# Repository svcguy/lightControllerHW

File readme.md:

Schematic and PCB for my workbench light controller

The workbench light is a 1m strip of APA102C Cool White LEDs, 144 LEDS/m.

The controller is a custom PCB that uses capacitive touch buttons and is based on a PIC16F1719

The light housing is made from an aluminum commercial door threshold and some 3/8" black gas piping.

This is a work-in-progress with more information to come

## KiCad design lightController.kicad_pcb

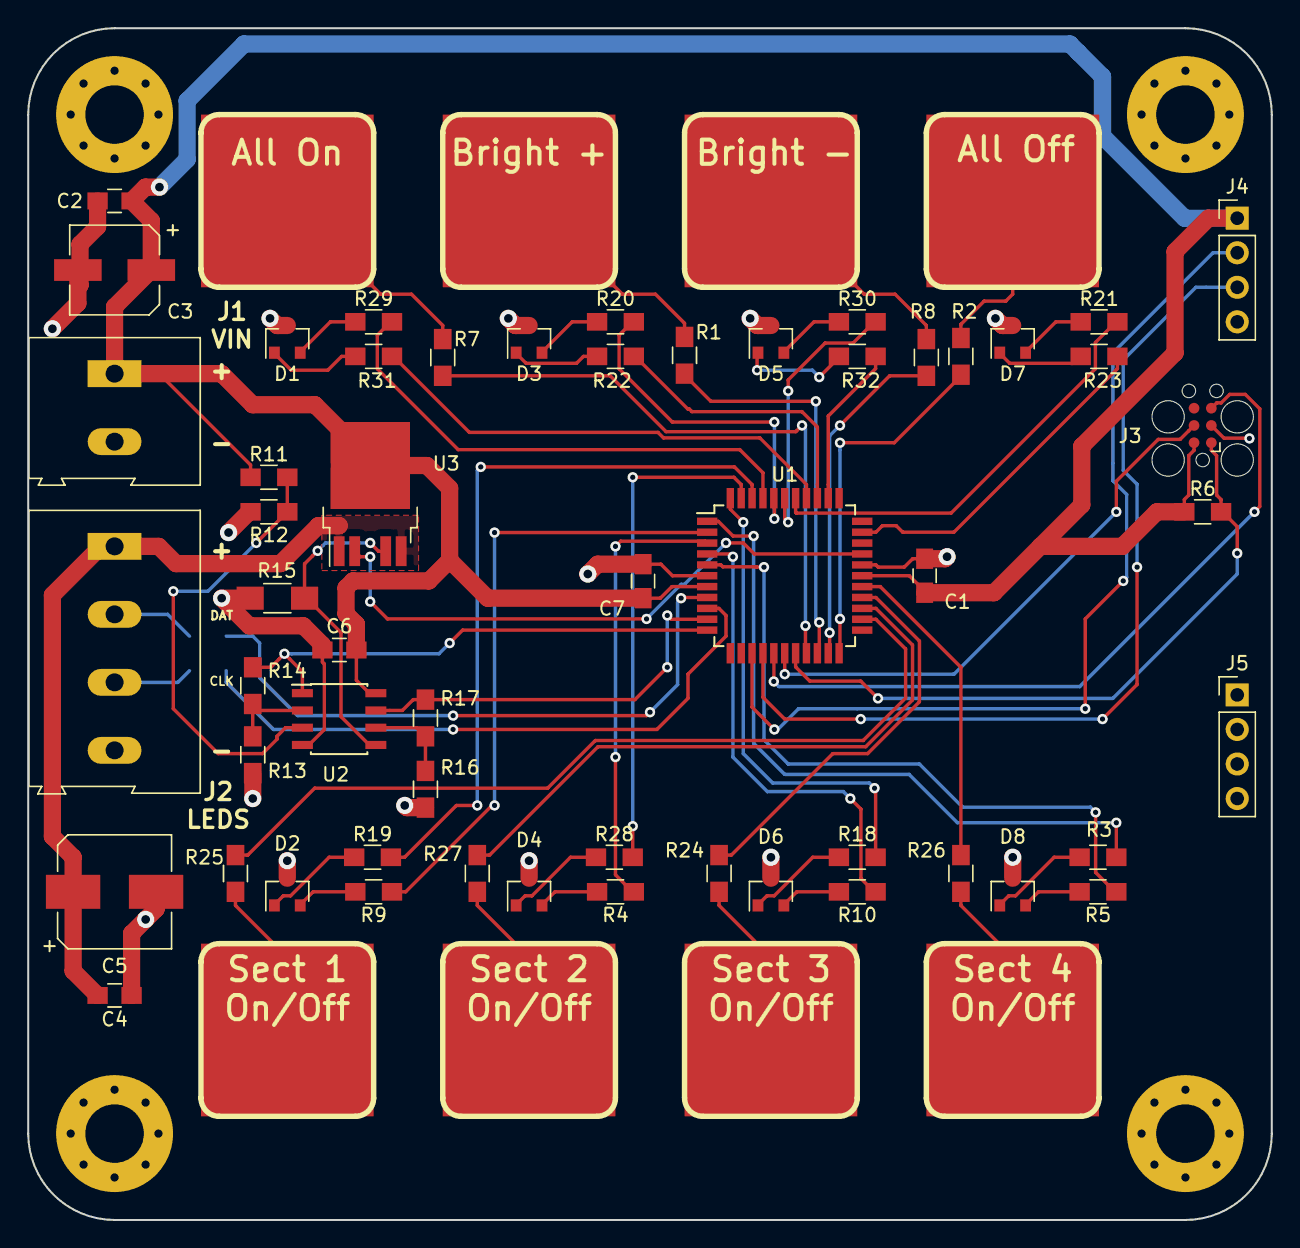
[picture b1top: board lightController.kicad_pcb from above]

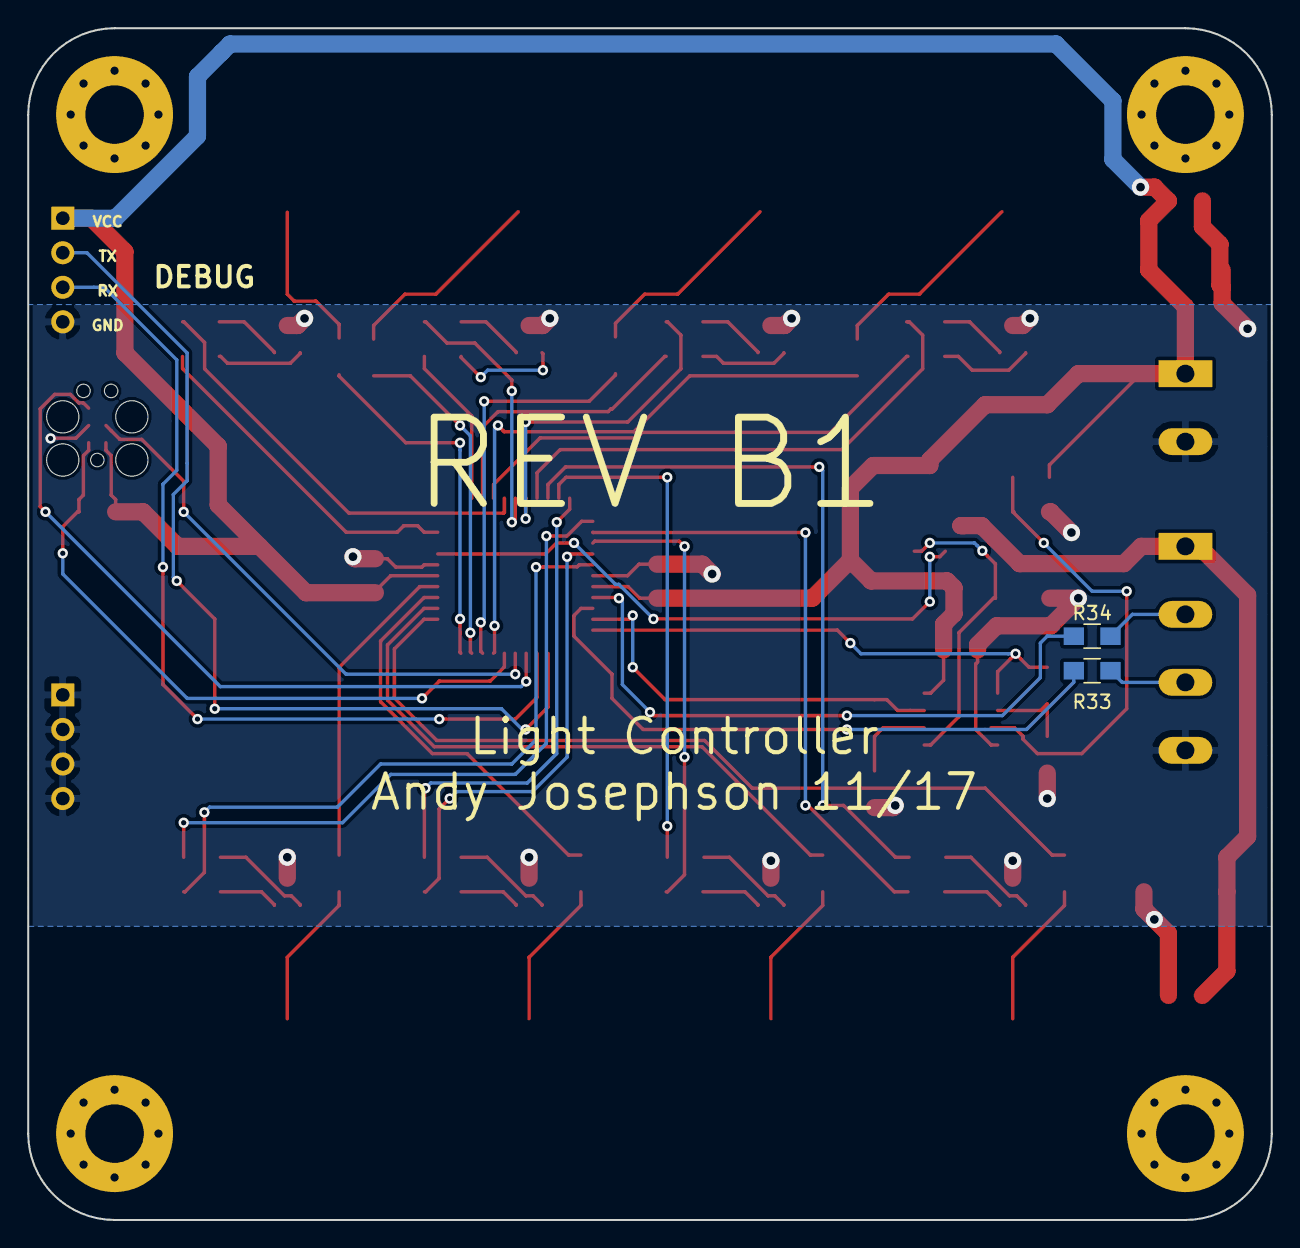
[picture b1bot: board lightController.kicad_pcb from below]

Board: 2 copper layers, 91.4 x 87.6 mm, 69 parts (2 on the bottom side), 67 nets.

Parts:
C1, C2, C4, C6, C7: 0.1uF; C_0805_HandSoldering
C3: 100uF; CP_Elec_6.3x5.3
C5: 1000uF; CP_Elec_8x10.5
D1: LED_LIGHT_ON; SOT-23
D2: LED_SECT_0; SOT-23
D3: LED_BRIGHT+; SOT-23
D4: LED_SECT_1; SOT-23
D5: LED_BRIGHT-; SOT-23
D6: LED_SECT_2; SOT-23
D7: LED_LIGHT_OFF; SOT-23
D8: LED_SECT_3; SOT-23
H1, H2, H3, H4: HOLE; MountingHole_4.3mm_M4_Pad_Via
J1: VIN; TerminalBlock_Altech_AK300-2_P5.00mm
J2: LED STRIP; TerminalBlock_Altech_AK300-4_P5.00mm
J3: ICSP; Tag-Connect_TC2030-IDC-FP
J4: DEBUG; Pin_Header_Straight_1x04_Pitch2.54mm
J5: GND; Pin_Header_Straight_1x04_Pitch2.54mm
R1, R2, R7, R8, R16, R24, R25, R26, R27, R33, R34: 1k; R_0805_HandSoldering
R3, R4, R5, R9, R10, R18, R19, R20, R21, R22, R23, R28, R29, R30, R31, R32: 180; R_0805_HandSoldering
R6: 10k; R_0805_HandSoldering
R11: 90.9k; R_0805_HandSoldering
R12: 90.9; R_0805_HandSoldering
R13: 1.1k; R_0805_HandSoldering
R14: 110k; R_0805_HandSoldering
R15: 1k; R_1206_HandSoldering
R17: 4.02k; R_0805_HandSoldering
SW1: LIGHT_ON; CAP_SENSE_PAD
SW2: SECT_0_ON; CAP_SENSE_PAD
SW3: BRIGHT+; CAP_SENSE_PAD
SW4: SECT_1_ON; CAP_SENSE_PAD
SW5: BRIGHT-; CAP_SENSE_PAD
SW6: SECT_2_ON; CAP_SENSE_PAD
SW7: LIGHT_OFF; CAP_SENSE_PAD
SW8: SECT_3_ON; CAP_SENSE_PAD
U1: PIC16(L)F1717/9; TQFP-44_10x10mm_Pitch0.8mm
U2: LM358; SOIC-8_3.9x4.9mm_Pitch1.27mm
U3: BTS6143; TO-252-5_TabPin3

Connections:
/CAP1: R7.2, SW1.1
/CAP2: R1.2, SW3.1
/CAP3: R8.2, SW5.1
/CAP4: R2.2, SW7.1
/CAP5: R25.1, SW2.1
/CAP6: R27.1, SW4.1
/CAP7: R24.1, SW6.1
/CAP8: R26.1, SW8.1
/DEBUG1: J4.2, U1.14
/DEBUG2: J4.3, U1.15
/I_SNS: R17.1, U1.10, U2.7
/LED_1_G: D1.2, R29.1
/LED_1_R: D1.1, R31.1
/LED_2_G: D3.2, R20.1
/LED_2_R: D3.1, R22.1
/LED_3_G: D5.2, R30.1
/LED_3_R: D5.1, R32.1
/LED_4_G: D7.2, R21.1
/LED_4_R: D7.1, R23.1
/LED_5V: C4.2, C5.1, J2.1, U3.1, U3.5
/LED_5_G: D2.2, R9.2
/LED_5_R: D2.1, R19.1
/LED_6_G: D4.2, R4.2
/LED_6_R: D4.1, R28.1
/LED_7_G: D6.2, R10.2
/LED_7_R: D6.1, R18.1
/LED_8_G: D8.2, R5.2
/LED_8_R: D8.1, R3.2
/LED_CLK: R33.1, U1.9
/LED_DAT: R34.1, U1.8
/PGC: J3.5, U1.16
/PGD: J3.4, U1.17
/PWR_EN: U1.30, U3.2
/V_SNS: R14.1, U1.11, U2.1
/~MCLR: J3.1, R6.2, U1.18
GND: C1.2, C2.1, C3.2, C4.1, C5.2, C6.1, C7.2, D1.3, D2.3, D3.3, D4.3, D5.3, D6.3, D7.3, D8.3, J1.2, J2.4, J3.3, J4.4, J5.1, J5.2, J5.3, J5.4, R12.2, R13.1, R15.2, R16.1, U1.6, U1.29, U2.4
unnamed: J2.2, R34.2
unnamed: J2.3, R33.2
unnamed: R1.1, U1.20
unnamed: R2.1, U1.22
unnamed: R3.1, U1.1
unnamed: R4.1, U1.3
unnamed: R5.1, U1.5
unnamed: R7.1, U1.19
unnamed: R8.1, U1.21
unnamed: R9.1, U1.2
unnamed: R10.1, U1.4
unnamed: R11.2, R12.1, U2.3
unnamed: R13.2, R14.2, U2.2
unnamed: R15.1, U2.5, U3.4
unnamed: R16.2, R17.2, U2.6
unnamed: R18.2, U1.44
unnamed: R19.2, U1.42
unnamed: R20.2, U1.40
unnamed: R21.2, U1.38
unnamed: R22.2, U1.36
unnamed: R23.2, U1.32
unnamed: R24.2, U1.26
unnamed: R25.2, U1.24
unnamed: R26.2, U1.27
unnamed: R27.2, U1.25
unnamed: R28.2, U1.43
unnamed: R29.2, U1.41
unnamed: R30.2, U1.39
unnamed: R31.2, U1.37
unnamed: R32.2, U1.35
VCC: C1.1, C2.2, C3.1, C6.2, C7.1, J1.1, J3.2, J4.1, R6.1, R11.1, U1.7, U1.28, U2.8, U3.3

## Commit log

2017-12-18 Initial Commit of version A1 files
2017-12-18 Add README and .gitignore
2017-12-20 Changed R15 and R17 to make current sense work
2017-12-23 Changed TX/RX to PORTB and I_SNS and PWR_EN accordingly Added SPI termination resistor footprints Added J5 GND pads
